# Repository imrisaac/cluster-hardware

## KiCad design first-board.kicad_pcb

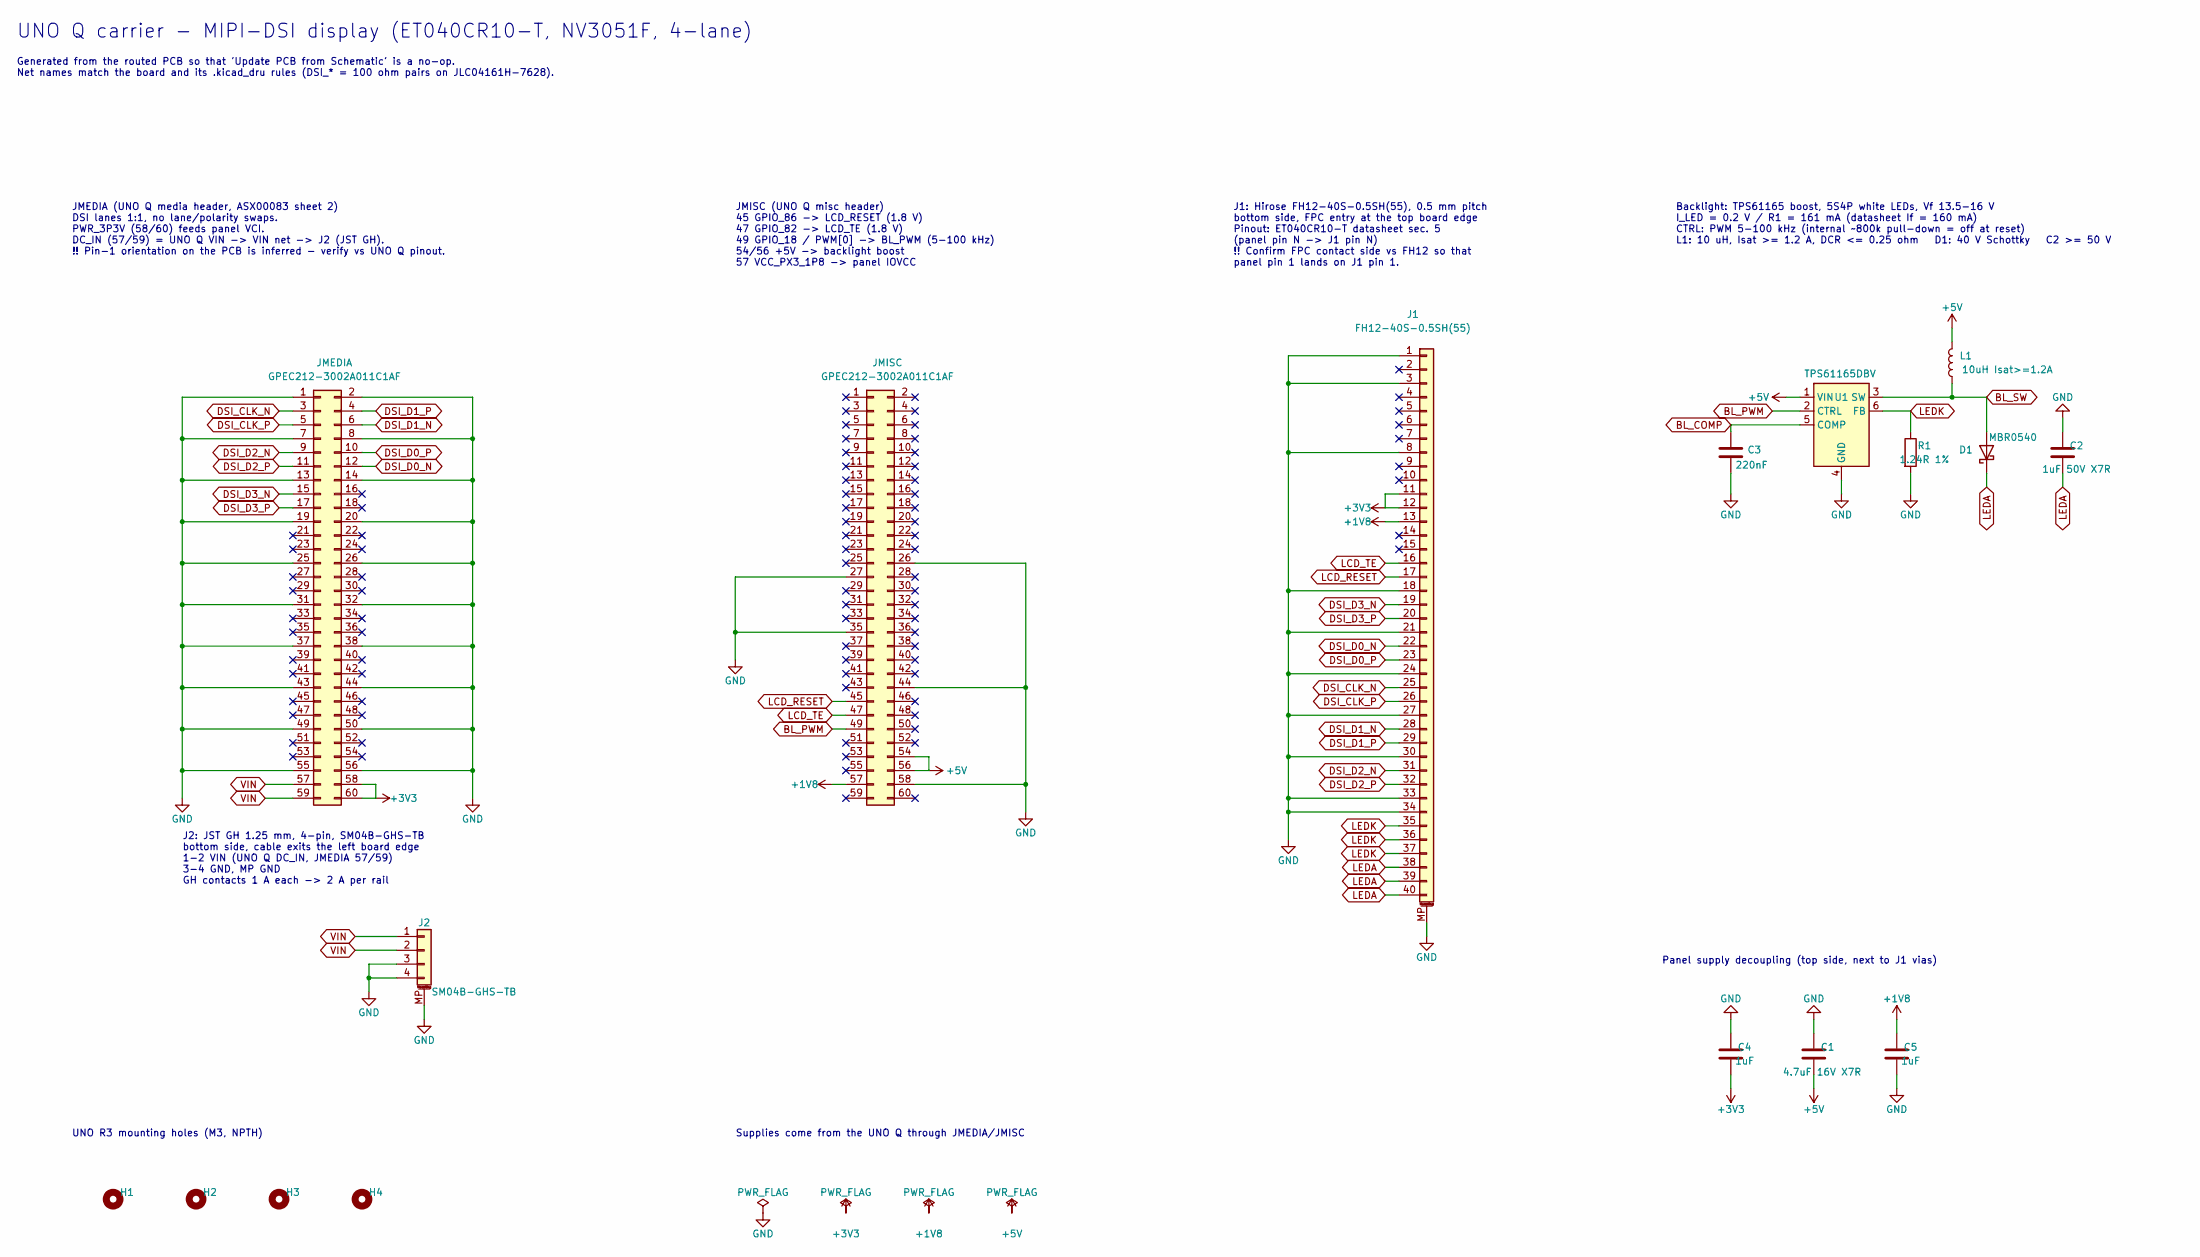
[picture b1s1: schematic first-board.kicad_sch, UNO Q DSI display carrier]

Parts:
C1: 4.7uF 16V X7R; C_0805_2012Metric
C2: 1uF 50V X7R; C_0805_2012Metric
C3: 220nF; C_0603_1608Metric
C4, C5: 1uF; C_0402_1005Metric
D1: MBR0540; D_SOD-123
H1, H2, H3, H4: MountingHole_M3; MountingHole_3.2mm_M3
J1: FH12-40S-0.5SH(55); Hirose_FH12-40S-0.5SH_1x40-1MP_P0.50mm_Horizontal
J2: SM04B-GHS-TB; JST_GH_SM04B-GHS-TB_1x04-1MP_P1.25mm_Horizontal
JMEDIA: GPEC212-3002A011C1AF; PinHeader_2x30_P1.27mm_Vertical_SMD
JMISC: GPEC212-3002A011C1AF; PinHeader_2x30_P1.27mm_Vertical_SMD
L1: 10uH Isat>=1.2A; L_Coilcraft_XAL4040-XXX
R1: 1.24R 1%; R_0603_1608Metric
U1: TPS61165DBV; SOT-23-6

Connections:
+1V8: C5.1, J1.13, JMISC.57
+3V3: C4.2, J1.11, J1.12, JMEDIA.58, JMEDIA.60
+5V: C1.2, JMISC.54, JMISC.56, L1.2, U1.1 (VIN)
BL_COMP: C3.2, U1.5 (COMP)
BL_PWM: JMISC.49, U1.2 (CTRL)
BL_SW: D1.2 (A), L1.1, U1.3 (SW)
DSI_CLK_N: J1.25, JMEDIA.3
DSI_CLK_P: J1.26, JMEDIA.5
DSI_D0_N: J1.22, JMEDIA.12
DSI_D0_P: J1.23, JMEDIA.10
DSI_D1_N: J1.28, JMEDIA.6
DSI_D1_P: J1.29, JMEDIA.4
DSI_D2_N: J1.31, JMEDIA.9
DSI_D2_P: J1.32, JMEDIA.11
DSI_D3_N: J1.19, JMEDIA.15
DSI_D3_P: J1.20, JMEDIA.17
GND: C1.1, C2.1, C3.1, C4.1, C5.2, J1.1, J1.3, J1.8, J1.18, J1.21, J1.24, J1.27, J1.30, J1.33, J1.34, J1.MP (MountPin), J2.3, J2.4, J2.MP (MountPin), JMEDIA.1, JMEDIA.2, JMEDIA.7, JMEDIA.8, JMEDIA.13, JMEDIA.14, JMEDIA.19, JMEDIA.20, JMEDIA.25, JMEDIA.26, JMEDIA.31, JMEDIA.32, JMEDIA.37, JMEDIA.38, JMEDIA.43, JMEDIA.44, JMEDIA.49, JMEDIA.50, JMEDIA.55, JMEDIA.56, JMISC.26, JMISC.27, JMISC.35, JMISC.44, JMISC.58, R1.2, U1.4 (GND)
LCD_RESET: J1.17, JMISC.45
LCD_TE: J1.16, JMISC.47
LEDA: C2.2, D1.1 (K), J1.38, J1.39, J1.40
LEDK: J1.35, J1.36, J1.37, R1.1, U1.6 (FB)
VIN: J2.1, J2.2, JMEDIA.57, JMEDIA.59

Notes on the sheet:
UNO R3 mounting holes (M3, NPTH)
Supplies come from the UNO Q through JMEDIA/JMISC
JMISC (UNO Q misc header) 45 GPIO_86 -> LCD_RESET (1.8 V) 47 GPIO_82 -> LCD_TE (1.8 V) 49 GPIO_18 / PWM[0] -> BL_PWM (5-100 kHz) 54/56 +5V -> backlight boost 57 VCC_PX3_1P8 -> panel IOVCC
UNO Q carrier - MIPI-DSI display (ET040CR10-T, NV3051F, 4-lane)
Generated from the routed PCB so that 'Update PCB from Schematic' is a no-op. Net names match the board and its .kicad_dru rules (DSI_* = 100 ohm pairs on JLC04161H-7628).
Backlight: TPS61165 boost, 5S4P white LEDs, Vf 13.5-16 V I_LED = 0.2 V / R1 = 161 mA (datasheet If = 160 mA) CTRL: PWM 5-100 kHz (internal ~800k pull-down = off at reset) L1: 10 uH, Isat >= 1.2 A, DCR <= 0.25 ohm D1: 40 V Schottky C2 >= 50 V
JMEDIA (UNO Q media header, ASX00083 sheet 2) DSI lanes 1:1, no lane/polarity swaps. PWR_3P3V (58/60) feeds panel VCI. DC_IN (57/59) = UNO Q VIN -> VIN net -> J2 (JST GH). !! Pin-1 orientation on the PCB is inferred - verify vs UNO Q pinout.
J1: Hirose FH12-40S-0.5SH(55), 0.5 mm pitch bottom side, FPC entry at the top board edge Pinout: ET040CR10-T datasheet sec. 5 (panel pin N -> J1 pin N) !! Confirm FPC contact side vs FH12 so that panel pin 1 lands on J1 pin 1.
Panel supply decoupling (top side, next to J1 vias)
J2: JST GH 1.25 mm, 4-pin, SM04B-GHS-TB bottom side, cable exits the left board edge 1-2 VIN (UNO Q DC_IN, JMEDIA 57/59) 3-4 GND, MP GND GH contacts 1 A each -> 2 A per rail

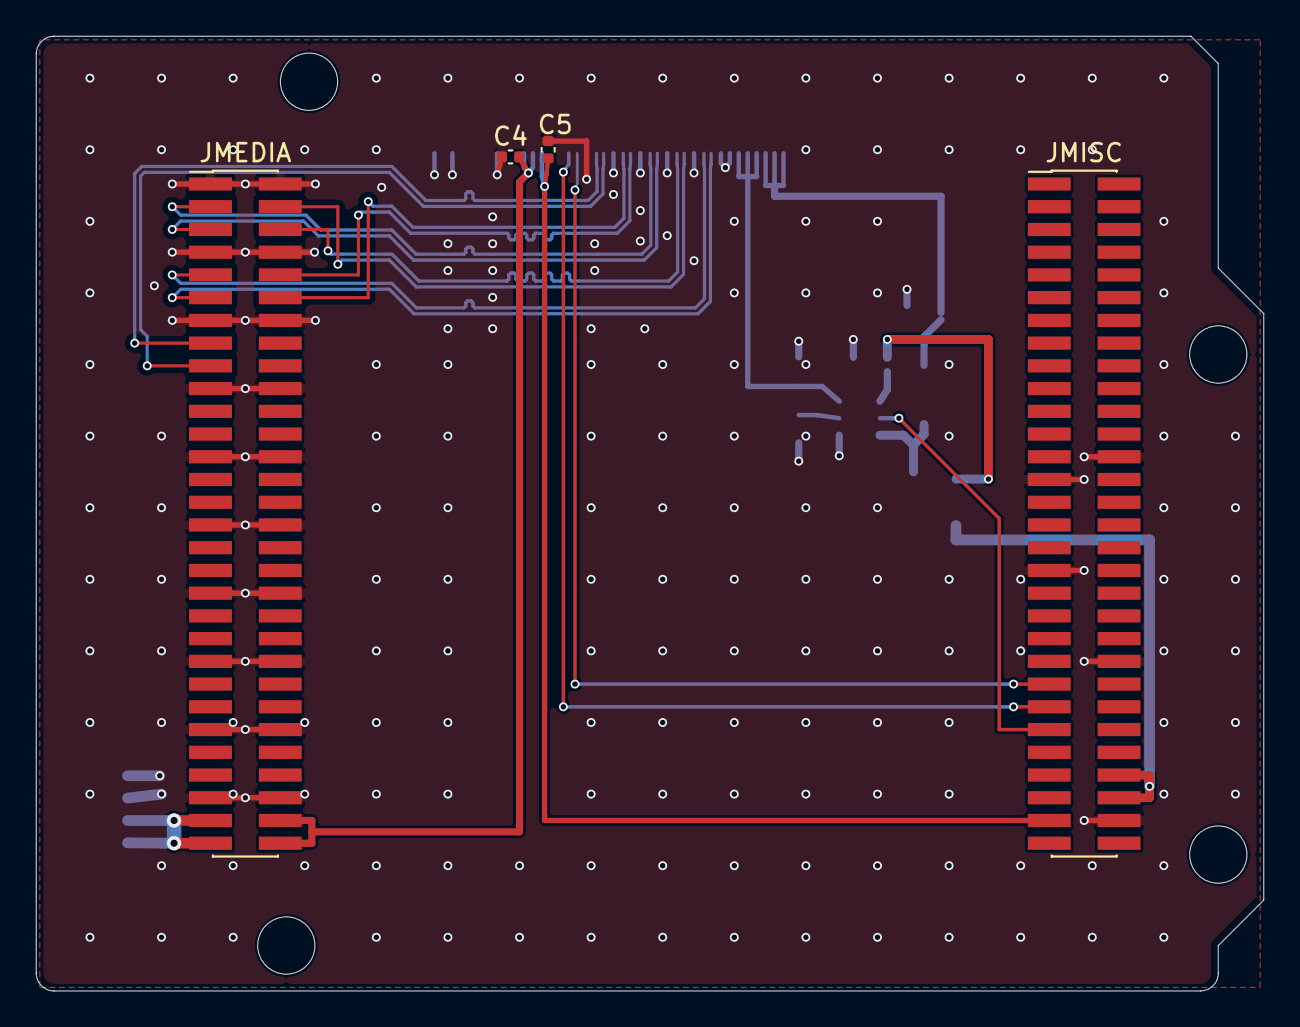
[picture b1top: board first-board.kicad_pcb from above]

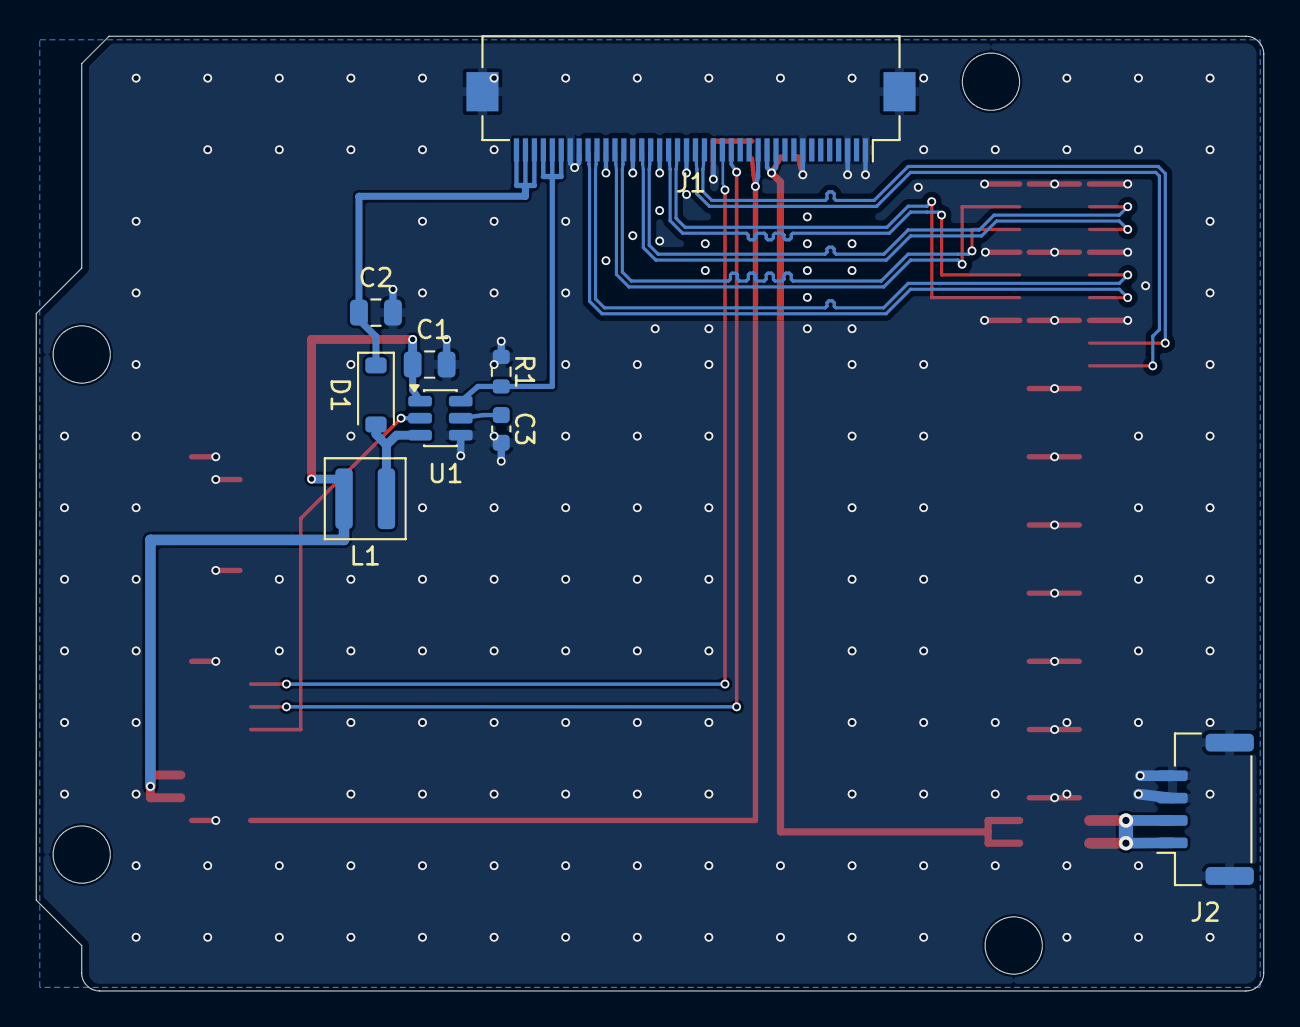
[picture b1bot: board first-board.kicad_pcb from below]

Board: 4 copper layers, 68.6 x 53.3 mm, 17 parts (9 on the bottom side), 22 nets.
